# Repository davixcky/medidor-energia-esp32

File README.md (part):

# Medidor de energía eléctrica no invasivo de dos canales con ESP32

**Avance 2 del proyecto de aula (ABPr) — Corte 2**

Sistemas Embebidos 1 · Ingeniería Electrónica · Universidad de la Costa (CUC) · Periodo 2026-2

**Integrantes:** David Orozco · Jose Torres · Leo Rojas

---

## Revisión B — fabricación e interfaz local

La revisión B incorpora gabinete PETG con tapa magnética, LCD Waveshare a color, cuatro
NeoPixels, piezo y encoder para brillo, sonido y umbral de alerta. Las comprobaciones son de
software y CAD; faltan montaje y validación eléctrica. La posición USB-C requiere medir la placa real.

- [Descargas v1.3.0: video con voz y música, CAD y archivos P2S](https://github.com/davixcky/medidor-energia-esp32/releases/tag/v1.3.0).
- [Ficha del dispositivo](freecad/revision-b/medidor-revB.pdf) y [guía de montaje](freecad/revision-b/LEER-ANTES-DE-IMPRIMIR.txt).
- [Firmware y uso del encoder](firmware/README.md#configuración-con-encoder-v130).
- [Fuentes del video](video/revision-b/LEEME.txt).

Los STL y fuentes editables están en Git. El video, la escena Blender y los paquetes de
fabricación se publican como archivos de la release; las cachés y fotogramas se regeneran.
La PCB principal conserva su revisión anterior: encoder, NeoPixels y piezo requieren el
cableado y circuito auxiliar indicados en la guía.

## Contenido

1. [Introducción](#1-introducción)
2. [Objetivos](#2-objetivos)
3. [Planteamiento del problema](#3-planteamiento-del-problema)
4. [Marco teórico](#4-marco-teórico)
5. [Estado del arte](#5-estado-del-arte)
6. [Listado de materiales](#6-listado-de-materiales)
7. [Componente técnico](#7-componente-técnico)
8. [Verificación de la metodología y del cronograma](#8-verificación-de-la-metodología-y-del-cronograma)
9. [Referencias](#9-referencias)
10. [Anexo: archivos fuente y cómo regenerar las ilustraciones](#10-anexo-archivos-fuente-y-cómo-regenerar-las-ilustraciones)

---

## 1. Introducción

Cuando una vivienda o un local comercial no cuenta con medición adicional, la factura informa el
consumo mensual total con hasta treinta días de retraso. Ese dato no permite identificar el consumo
por carga ni por hora, y dificulta evaluar las medidas de ahorro. En la región Caribe, el uso del aire
acondicionado durante el año representa una parte importante del consumo [1].

Este proyecto tiene como objetivo desarrollar un medidor de energía monofásico de 120 V / 60 Hz basado en el microcontrolador
**ESP32**. La medida es **no invasiva**: la corriente se obtiene con pinzas de núcleo partido
**SCT-013-000** que abrazan el conductor de fase sin abrir el circuito, y la tensión con un módulo
**ZMPT101B** que la reduce mediante un transformador aislado. El sistema tiene **dos canales de
corriente** —CH1 para el total del tablero y CH2 para un subcircuito, por ejemplo el del aire
acondicionado— y **un canal de tensión**. El ESP32 digitaliza las tres señales con su convertidor
interno, calcula tensión y corriente eficaces, potencia activa, reactiva y aparente y factor de
potencia, y publica los resultados por Wi-Fi.

Este documento corresponde al segundo avance. Presenta el diseño eléctrico en KiCad, los cálculos de
los componentes, el diseño y los archivos de fabricación de la PCB de una cara, el diseño del gabinete,
el protocolo de pruebas y el estado del cronograma. El montaje del prototipo está pendiente. El
*firmware* y la plataforma se han probado con señales sintéticas y datos simulados; falta validarlos
con el equipo físico en el tercer corte.

## 2. Objetivos

### 2.1. Objetivo general

Desarrollar un medidor de energía eléctrica monofásico y no invasivo, basado en ESP32, con dos canales
de corriente y un canal de tensión aislado, montado en una PCB de una cara dentro de un gabinete con la
zona de red separada, que calcule tensión y corriente eficaces, potencias activa, reactiva y aparente y
factor de potencia por canal, y los publique por Wi-Fi.

### 2.2. Objetivos específicos

1. **Diseñar** la cadena de acondicionamiento (resistencia de carga, polarización, filtro antialias y
   protección) y el esquemático completo en KiCad, sin errores en la verificación eléctrica (ERC), de
   modo que 60 A en CH1 y 30 A en CH2 queden dentro de la zona lineal del ADC1 del ESP32.
2. **Construir** el prototipo en una PCB de una cara fabricada por el grupo, integrado con el microcontrolador dentro del
   gabinete, y aprobar la verificación previa a la energización y la prueba de resistencia
   (*HardExplosion*).
3. **Programar y validar** el *firmware* de adquisición y cálculo (8.000 muestras por segundo por canal,
   ventanas de ciclos completos) y el envío de los registros a la plataforma web, con un error de potencia activa de ±3 % o
   menos frente a una carga resistiva de potencia conocida entre 1 A y 30 A.

## 3. Planteamiento del problema

El Sistema Interconectado Nacional sigue aumentando su demanda año tras año, y la región Caribe consume
una fracción de la energía nacional mayor que su fracción de la población; en los edificios
comerciales de la región el aire acondicionado representa en promedio cerca de la mitad del consumo
total [1]. La factura residencial o comercial presenta el consumo mensual registrado por el contador, sin
desglosarlo por circuito o equipo.

Esa lectura tiene tres limitaciones:

- **Resolución temporal de un mes.** No muestra los ciclos diario y semanal, que son los que dominan en
  un clima sin estaciones.
- **Agregación total.** No distingue qué circuito o qué equipo produjo el consumo, de modo que la factura
  no puede atribuirse a cargas concretas.
- **Latencia.** El usuario conoce su consumo hasta treinta días después, y una acción de ahorro no se
  puede verificar antes del siguiente ciclo de facturación.

Algunos medidores comerciales con Wi-Fi permiten consultar el consumo, pero tienen una arquitectura
cerrada y no dan acceso a la forma de onda ni al método de cálculo. Esto limita su uso para estudiar
la cadena de medición en el curso de sistemas embebidos, desde el sensor y el acondicionamiento hasta
la conversión analógica-digital, el procesamiento y la comunicación.

**Pregunta del proyecto:** ¿cómo medir, con un microcontrolador de bajo costo y sin intervenir la
instalación, el consumo de una edificación por circuito y en tiempo casi real, de forma segura para el
usuario y con un error conocido?

> **Alineación con el primer entregable.** El primer entregable definió un nodo ESP32 con tres pinzas y
> un canal de tensión. Para el alcance de esta asignatura se implementan **dos canales de corriente**
> (total y un subcircuito) y el tercero queda como reserva cableada en el conector J7, que expone las
> entradas GPIO34, GPIO32 y GPIO33 del ADC1 (sección 7.3). El problema, la arquitectura y los criterios
> de seguridad no cambian.

## 4. Marco teórico

### 4.1. Magnitudes eléctricas en régimen periódico

Para una tensión $v(t)$ y una corriente $i(t)$ periódicas de periodo $T$ (16,67 ms a 60 Hz), los valores
eficaces y la potencia activa se definen como [6]:

$$V_{rms} = \sqrt{\frac{1}{T}\int_0^T v^2(t)\,dt}, \qquad I_{rms} = \sqrt{\frac{1}{T}\int_0^T i^2(t)\,dt}, \qquad P = \frac{1}{T}\int_0^T v(t)\,i(t)\,dt$$

La potencia aparente es $S = V_{rms} I_{rms}$, el factor de potencia es $FP = P/S$ y, en régimen
sinusoidal, la potencia reactiva es $Q = \sqrt{S^2 - P^2}$. Con muestras discretas tomadas a la
frecuencia $f_s$, las integrales se reemplazan por sumas sobre un número **entero** de ciclos, lo que
evita el error de truncamiento de la ventana:

$$V_{rms} \approx \sqrt{\frac{1}{N}\sum_{n=0}^{N-1} v_n^2}, \qquad P \approx \frac{1}{N}\sum_{n=0}^{N-1} v_n\, i_n$$

La norma IEEE 1459 [6] extiende estas definiciones a señales no sinusoidales, en las que aparecen
armónicos; es el caso de las fuentes conmutadas y de los equipos con variador de frecuencia.

### 4.2. Transformador de corriente de núcleo partido

Un transformador de corriente (TC) entrega en su secundario una corriente proporcional a la del
primario, en la relación inversa del número de espiras. El SCT-013-000 tiene relación 100 A : 50 mA, es
decir $N = 2000$ espiras, y **no incluye resistencia de carga interna** [2]. El conductor de fase que
atraviesa el núcleo actúa como primario de una sola espira:

$$I_s = \frac{I_p}{N}$$

Para convertir esa corriente en tensión se conecta una resistencia de carga (en inglés, *burden*)
$R_b$ entre los terminales del secundario: $V_b = I_s R_b$.

**Riesgo del secundario abierto.** Si el secundario queda abierto mientras el primario conduce, toda la
fuerza magnetomotriz del primario magnetiza el núcleo, este se satura y en los terminales aparecen
picos de tensión peligrosos para las personas y para el ADC. Por eso la resistencia de carga va soldada
directamente en el conector y nunca en un cable que se pueda desconectar [10].

### 4.3. Medición aislada de la tensión

El ZMPT101B es un transformador de tensión de pequeña señal, con relación 1000:1000 y aislamiento
galvánico entre primario y secundario [3]. El módulo comercial agrega en serie con el primario una
resistencia que limita la corriente, y en el secundario un amplificador LM358 con un potenciómetro de
ganancia. La salida es una sinusoide montada sobre la mitad de la tensión de alimentación, 2,5 V si el
módulo se alimenta con 5 V. Es la **única** pieza del sistema conectada galvánicamente a la red; todo
lo demás opera en muy baja tensión.

### 4.4. Muestreo, aliasing y filtro antialias

El teorema de muestreo [9] exige $f_s > 2 f_{max}$ para reconstruir una señal sin ambigüedad. Si se
quieren observar armónicos hasta el orden 50 (3.000 Hz), se necesita $f_s > 6.000$ muestras/s. El
proyecto usa **8.000 muestras/s por canal**, es decir 133 muestras por ciclo de 60 Hz. Las componentes
por encima de $f_s/2$ se "pliegan" dentro de la banda útil. Para evitarlo, cada canal tiene un filtro RC
pasa-bajas de primer orden:

$$f_c = \frac{1}{2\pi R C}$$

Como la potencia activa depende del producto $v \cdot i$, un desfase $\Delta\varphi$ entre los filtros de
tensión y de corriente produce un error relativo en $P$ cercano a $\tan\varphi \cdot \Delta\varphi$. Por eso
los tres filtros deben tener constantes de tiempo casi iguales.

### 4.5. ADC del ESP32

El ESP32 tiene dos convertidores SAR de 12 bits. El **ADC2 no se puede usar mientras el Wi-Fi está
activo**, porque el controlador de radio lo ocupa [5]; en consecuencia, todas las entradas analógicas de
este proyecto están en el **ADC1** (GPIO32 a GPIO39). Con atenuación de 11 dB el rango útil y lineal
va de unos 0,15 V a 2,45 V [5]. Fuera de ese rango la curva de conversión se vuelve no lineal. Las
señales bipolares de la red se desplazan entonces a un nivel de reposo positivo (polarización) para que
la excursión completa caiga dentro de esa ventana.

### 4.6. Seguridad eléctrica

El Reglamento Técnico de Instalaciones Eléctricas (RETIE) [8] establece la separación entre circuitos de
red y de muy baja tensión (MBT), la protección contra sobrecorriente y el código de colores de los
conductores. El diseño del prototipo contempla cuatro criterios:

1. La red de 120 V nunca entra a la PCB: llega solo al módulo ZMPT101B, ubicado en un
   compartimento separado del gabinete por un tabique.
2. La rama de tensión está protegida con un fusible lento de 500 mA.
3. Las pinzas abrazan únicamente el conductor de fase y no se abre ningún circuito para instalarlas.
4. No se energiza el equipo sin una verificación de aislamiento firmada por dos integrantes
   (sección 7.9).

## 5. Estado del arte

La **Tabla 1** resume soluciones comerciales y abiertas para medir consumo eléctrico, comparadas en las
características que interesan a este proyecto.

**Tabla 1.** Comparación de medidores de energía existentes.

| Solución | Medición | Canales | Procesamiento y comunicación | Acceso a la forma de onda | Observación |
|---|---|---|---|---|---|
| Shelly EM [11] | Pinzas de corriente y tensión directa | 2 | Integrado; Wi-Fi | No | Comercial, muy cercana en alcance a este proyecto |
| Emporia Vue [12] | 2 TC principales y hasta 16 TC por circuito | Hasta 18 | Integrado; Wi-Fi y nube propia | No | Cerrado, orientado al consumidor |
| Sense [13] | 2 TC de 200 A | 2 | Muestreo de alta frecuencia y desagregación de cargas | No para el usuario | Identifica equipos por su firma eléctrica (NILM) [7] |
| IoTaWatt [14] | TC y transformador de tensión externo | 14 | ESP8266 con ADC externo; Wi-Fi | Parcial | *Hardware* y *software* abiertos |
| OpenEnergyMonitor emonTx [10] | TC SCT-013 y adaptador de CA | 3 a 6 | Microcontrolador AVR; radio | Sí | Referencia de diseño del acondicionamiento con resistencia de carga y divisor de polarización |
| PZEM-004T v3.0 [15] | TC propio y conexión directa a red | 1 | Integrado; Modbus-RTU | No | Módulo económico, entrega valores ya calculados una vez por segundo |
| Integrado de metrología ATM90E32AS [16] | Requiere acondicionamiento externo | 3 fases | ADC sigma-delta simultáneos; SPI | No (registros) | Exactitud de contador; procesamiento interno no accesible; requiere importación |
| **Este proyecto** | **2 SCT-013-000 + ZMPT101B** | **2 + 1 tensión** | **ESP32, ADC1 interno; Wi-Fi y HTTP** | **Sí, 8.000 muestras/s por canal** | **Arquitectura abierta; cálculo implementado por el grupo** |

Fuente: elaboración propia a partir de la documentación de cada producto.

Del análisis se concluye que:

- Las soluciones comerciales sin acceso a las muestras ni al método de cálculo limitan el estudio
  de la cadena de adquisición, que forma parte del objetivo académico de la asignatura.
- Los proyectos abiertos (OpenEnergyMonitor, IoTaWatt) validan el enfoque de **pinza SCT-013 +
  resistencia de carga + divisor de polarización + ADC del microcontrolador**, que es el adoptado aquí.
- El acceso a las muestras sin procesar permitiría aplicar técnicas de desagregación de cargas
  (NILM) [7], que los módulos cerrados como el PZEM-004T no permiten.

## 6. Listado de materiales

La **Tabla 2** lista todos los materiales del prototipo. Las referencias de componente coinciden con el
esquemático de la Ilustración 2.

**Tabla 2.** Lista de materiales.

| # | Referencia | Descripción | Cant. | Uso |
|---:|---|---|---:|---|
| 1 | U1 | Tarjeta ESP32-DevKitC V4, 38 pines (ESP32-WROOM-32) | 1 | Microcontrolador, ADC y Wi-Fi |
| 2 | — | Pinza de corriente YHDC SCT-013-000, 100 A : 50 mA, sin resistencia de carga | 2 | Medición de corriente CH1 y CH2 |
| 3 | U2 | Módulo sensor de tensión ZMPT101B (con LM358 y potenciómetro) | 1 | Medición aislada de tensión |
| 4 | — | Pantalla LCD Waveshare de 1,9" (ST7789V2, 170 × 320, SPI), con su cable de 8 hilos | 1 | Lectura local |
| 5 | — | Baquelita de una cara de 10 × 15 cm (FR-2 o FR-4), percloruro férrico, papel de transferencia y alambre UTP para los puentes | 1 | PCB del circuito (sección 7.7) |
| 6 | — | Adaptador 100–240 V CA a 5,1 V CC (5,0–5,25 V), 2 A o más, con aislamiento certificado | 1 | Alimentación |
| 7 | — | *Jack* de panel para alimentación de 5,5 × 2,1 mm | 1 | Entrada de 5 V en el gabinete |
| 8 | J2, J3 | *Jack* estéreo hembra de 3,5 mm para panel | 2 | Conexión de las pinzas |
| 9 | J1 | Bornera de 2 polos, paso 5,08 mm | 1 | Entrada de 5 V en la placa |
| 10 | J5 | Bornera de 3 polos, paso 5,08 mm | 1 | Cable del módulo ZMPT101B |
| 11 | J4 | Regleta de 2 bornes de tornillo | 1 | Empalme de fase y neutro en la zona de red |
| 12 | F1 | Portafusible de 5 × 20 mm y fusible lento T 500 mA, 250 V | 1 + 1 de repuesto | Protección de la rama de tensión |
| 13 | F2 | Fusible PTC de rearme automático MF-R110 (1,1 A de mantenimiento) | 1 | Protección contra cortocircuito en 5 V |
| 14 | D1 | Diodo Schottky 1N5819 | 1 | Protección contra polaridad invertida |
| 15 | D2–D7 | Diodo Schottky BAT85 (DO-35) | 6 | Recorte de sobretensión en las entradas del ADC |
| 16 | R1 | Resistencia 22 Ω, 1 %, película metálica, 1/4 W | 1 | Resistencia de carga CH1 |
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
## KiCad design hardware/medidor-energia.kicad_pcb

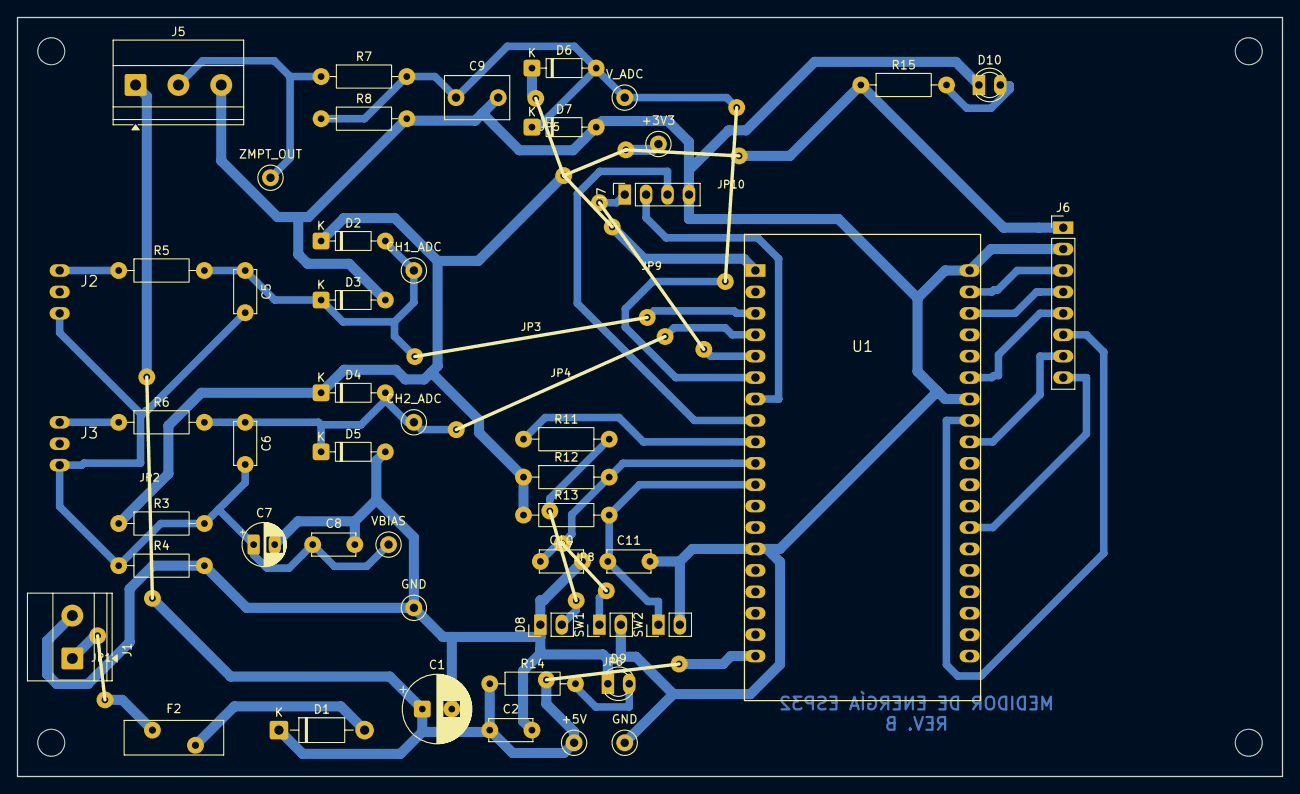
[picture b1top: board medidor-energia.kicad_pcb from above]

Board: 2 copper layers, 150.0 x 90.0 mm, 63 parts (0 on the bottom side), 27 nets.

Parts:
C1: 470u 10V; CP_Radial_D8.0mm_P3.50mm
C2, C8, C10, C11: 100n; C_Disc_D5.0mm_W2.5mm_P5.00mm
C5, C6: 47n C0G; C_Disc_D5.0mm_W2.5mm_P5.00mm
C7: 10u 16V; CP_Radial_D5.0mm_P2.50mm
C9: 27n C0G; C_Disc_D7.5mm_W5.0mm_P5.00mm
D1: 1N5819; D_DO-41_SOD81_P10.16mm_Horizontal
D2, D3, D4, D5, D6, D7: BAT85; D_DO-35_SOD27_P7.62mm_Horizontal
D8: LED verde 5 mm (panel); PinHeader_1x02_P2.54mm_Vertical
D9: LED rojo 3 mm; LED_D3.0mm
D10: LED verde 3 mm; LED_D3.0mm
F2: PTC 1,1 A (MF-R110); Fuse_BelFuse_0ZRE0040FF_L11.5mm_W3.8mm
H1, H2, H3, H4: MountingHole_3.2mm_M3
J1: Bornera 5 V; TerminalBlock_Phoenix_MKDS-1,5-2-5.08_1x02_P5.08mm_Horizont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
J2: Jack 3,5 mm de panel (pinza SCT-013-000 CH1); Cable_Jack_Panel
J3: Jack 3,5 mm de panel (pinza SCT-013-000 CH2); Cable_Jack_Panel
J5: Bornera ZMPT; TerminalBlock_Phoenix_MKDS-1,5-3-5.08_1x03_P5.08mm_Horizont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
J6: LCD (VCC GND DIN CS DC BL CLK RST); PinHeader_1x08_P2.54mm_Vertical
J7: Reserva ADC1; PinSocket_1x04_P2.54mm_Vertical
JP1, JP2, JP3, JP4, JP5, JP6, JP7, JP8, JP9, JP10: puente; Puente_alambre
R3: 15k 1%; R_Axial_DIN0207_L6.3mm_D2.5mm_P10.16mm_Horizontal
R4: 10k 1%; R_Axial_DIN0207_L6.3mm_D2.5mm_P10.16mm_Horizontal
R5, R6: 3,3k 1%; R_Axial_DIN0207_L6.3mm_D2.5mm_P10.16mm_Horizontal
R7: 11k 1%; R_Axial_DIN0207_L6.3mm_D2.5mm_P10.16mm_Horizontal
R8: 13k 1%; R_Axial_DIN0207_L6.3mm_D2.5mm_P10.16mm_Horizontal
R11: 330; R_Axial_DIN0207_L6.3mm_D2.5mm_P10.16mm_Horizontal
R12, R13: 10k; R_Axial_DIN0207_L6.3mm_D2.5mm_P10.16mm_Horizontal
R14: 1k; R_Axial_DIN0207_L6.3mm_D2.5mm_P10.16mm_Horizontal
R15: 470; R_Axial_DIN0207_L6.3mm_D2.5mm_P10.16mm_Horizontal
SW1, SW2: Pulsador de panel 12 mm NA; PinHeader_1x02_P2.54mm_Vertical
TP1: +5V; TestPoint_Loop_D2.50mm_Drill1.0mm
TP2: +3V3; TestPoint_Loop_D2.50mm_Drill1.0mm
TP3: VBIAS; TestPoint_Loop_D2.50mm_Drill1.0mm
TP4: CH1_ADC; TestPoint_Loop_D2.50mm_Drill1.0mm
TP5: CH2_ADC; TestPoint_Loop_D2.50mm_Drill1.0mm
TP6: ZMPT_OUT; TestPoint_Loop_D2.50mm_Drill1.0mm
TP7: V_ADC; TestPoint_Loop_D2.50mm_Drill1.0mm
TP8, TP9: GND; TestPoint_Loop_D2.50mm_Drill1.0mm
U1: ESP32-DevKitC V4 (38 pines); ESP32-DevKitC-38_Zocalo

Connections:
+3V3: D2.1, D4.1, D6.1, J6.1, JP5.1, R3.1, R12.1, R13.1, R15.1, TP2.1, U1.1
+5V: C1.1, C2.1, D1.1, J5.1, JP2.1, JP6.1, R14.1, TP1.1, U1.19
/CH1_ADC: C5.1, D2.2, D3.1, JP3.1, R5.2, TP4.1, U1.3
/CH2_ADC: C6.1, D4.2, D5.1, JP4.1, R6.2, TP5.1, U1.4
/LCD_BL: J6.6, U1.27
/LCD_CLK: J6.7, U1.28
/LCD_CS: J6.4, U1.22
/LCD_DC: J6.5, U1.25
/LCD_DIN: J6.3, U1.21
/LCD_RST: J6.8, U1.32
/LED_EST: R11.1, U1.9
/RES_IO32: J7.2, U1.7
/RES_IO33: J7.3, U1.8
/RES_IO34: J7.1, JP9.1, U1.5
/SW1: C10.1, JP8.1, R12.2, SW1.1, U1.10
/SW2: C11.1, R13.2, SW2.1, U1.11
/VBIAS: C5.2, C6.2, C7.1, C8.1, J2.S, J3.S, R3.2, R4.1, TP3.1
/V_ADC: C9.1, D6.2, D7.1, JP10.1, R7.2, R8.1, TP7.1, U1.6
/ZMPT_OUT: J5.2, R7.1, TP6.1
GND: C1.2, C2.2, C7.2, C8.2, C9.2, C10.2, C11.2, D3.2, D5.2, D7.2, D8.1, D9.1, D10.1, J1.2, J5.3, J6.2, J7.4, R4.2, R8.2, SW1.2, SW2.2, TP8.1, TP9.1, U1.14, U1.20, U1.26
unnamed: D1.2, F2.2
unnamed: D8.2, JP7.1, R11.2
unnamed: D9.2, R14.2
unnamed: D10.2, R15.2
unnamed: F2.1, J1.1, JP1.1
unnamed: J2.T, R5.1
unnamed: J3.T, R6.1

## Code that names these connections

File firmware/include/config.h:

// Configuración del hardware y constantes de calibración.
// Los pines coinciden con la Tabla 3 del documento y con el esquemático.
#pragma once
#include <driver/adc.h>

// ---- Entradas analógicas (solo ADC1: el ADC2 no funciona con Wi-Fi)
constexpr adc1_channel_t ADC_CH1 = ADC1_CHANNEL_0;  // GPIO36, pinza CH1 (total)
constexpr adc1_channel_t ADC_CH2 = ADC1_CHANNEL_3;  // GPIO39, pinza CH2 (subcircuito)
constexpr adc1_channel_t ADC_V   = ADC1_CHANNEL_7;  // GPIO35, ZMPT101B

// ---- Interfaz local
constexpr int ENCODER_EDGES_PER_DETENT = 4; // elegir 2 si la ficha indica medio ciclo por paso
static_assert(ENCODER_EDGES_PER_DETENT == 2 || ENCODER_EDGES_PER_DETENT == 4, "Encoder: 2 o 4 flancos por paso");
constexpr int PIN_ENC_A = 32;
constexpr int PIN_ENC_B = 33;
constexpr int PIN_ENC_SW = 16; // ESP32-WROOM; no WROVER con PSRAM en GPIO16
constexpr int PIN_NEOPIXEL = 13; // módulo auxiliar, vía 74AHCT125 a 5 V
constexpr int PIN_BUZZER = 14;   // piezo pasivo vía transistor; PWM canal 2
constexpr int PIN_LED = 25;
constexpr int PIN_SW1 = 26;   // menú / canal (activo en bajo, pull-up externo de 10 kΩ)
constexpr int PIN_SW2 = 27;   // confirmar / tara
// LCD Waveshare de 1,9" (ST7789V2, 170 × 320) por SPI. Todos los pines están en el mismo lado
// de la tarjeta (J3 del DevKitC); se evitan GPIO5 y GPIO15, que son pines de arranque.
constexpr int PIN_LCD_CLK = 18;   // SCK del VSPI
constexpr int PIN_LCD_DIN = 23;   // MOSI del VSPI
constexpr int PIN_LCD_CS = 22;
constexpr int PIN_LCD_DC = 21;
constexpr int PIN_LCD_RST = 4;
constexpr int PIN_LCD_BL = 19;    // luz de fondo, con PWM
constexpr uint32_t LCD_SPI_HZ = 40000000;

// ---- Muestreo
constexpr uint32_t FS_HZ = 8000;        // muestras por segundo y por canal
constexpr int CICLOS_VENTANA = 60;      // ventana de 60 ciclos enteros (1 s a 60 Hz)
constexpr uint32_t DESCARTE_MS = 500;   // espera a que se estabilice VBIAS al encender

// ---- Calibración nominal. Son los valores por omisión: los que se miden en el banco se guardan en
// la memoria no volátil desde la consola serie (comando «cal», ver README del firmware) y no hace
// falta recompilar.
// Corriente: A de primario por voltio en el pin = relación 2000 / resistencia de carga.
constexpr float K_I1 = 2000.0f / 22.0f;   // CH1, burden 22 Ω
constexpr float K_I2 = 2000.0f / 47.0f;   // CH2, burden 47 Ω
// Tensión: V de red por voltio en el pin. 120 V eficaces → 0,352 V pico en el pin
// (potenciómetro del módulo en 0,65 V pico y divisor 13/24): 169,7 / 0,352 = 482.
constexpr float K_V = 482.0f;
// Corrección de fase en grados a 60 Hz: de cada pinza (positivo = la corriente adelanta) y del
// canal de tensión, transformador y LM358 del ZMPT101B (positivo = la tensión adelanta). Se mide
// en el banco con una carga inductiva o contra el PZEM-004T; con carga resistiva no se ve.
constexpr float FASE_CT1_GRADOS = 0.0f;
constexpr float FASE_CT2_GRADOS = 0.0f;
constexpr float FASE_V_GRADOS = 0.0f;
// Constante de tiempo de los filtros antialias (para compensar armónicos en el THD).
constexpr float TAU_FILTRO_S = 156e-6f;

// ---- Alerta local (el servidor calcula el umbral P95; esto es el respaldo sin red)
constexpr float UMBRAL_ALERTA_W = 2000.0f;
constexpr uint32_t ALERTA_SOSTENIDA_S = 300;

// ---- Red
constexpr uint32_t ENVIO_CADA_MS = 5000;    // lote de registros cada 5 s
constexpr size_t BUFER_REGISTROS = 1200;    // 20 min sin red en RAM (48 kB)

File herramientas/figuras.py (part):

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    ct2  [label="Pinza SCT-013-000 CH2\n(subcircuito, 0–30 A)", fillcolor="#fff8e1"];
    b1   [label="Burden 22 Ω\n+ RC 3,3 kΩ / 47 nF\n+ recorte BAT85", fillcolor="#fff8e1"];
    b2   [label="Burden 47 Ω\n+ RC 3,3 kΩ / 47 nF\n+ recorte BAT85", fillcolor="#fff8e1"];
    bias [label="VBIAS 1,32 V\ndivisor 15k/10k", fillcolor="#f3e5f5"];
    div  [label="Divisor 11k/13k\n+ C 27 nF\n+ recorte BAT85", fillcolor="#e8f5e9"];
    esp  [label="U1  ESP32-DevKitC V4\nADC1 12 bit · Wi-Fi\nGPIO36 / 39 / 35", fillcolor="#e3f2fd", penwidth=2];
    oled [label="LCD 1,9\" ST7789V2\n170 × 320, SPI", fillcolor="#e3f2fd"];
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  ct1 -> b1 [label="0–30 mA", color="#b8860b"];
  ct2 -> b2 [label="0–15 mA", color="#b8860b"];
  bias -> b1 [color="#8e24aa"]; bias -> b2 [color="#8e24aa"];
  b1 -> esp [label="CH1_ADC\nGPIO36", color="#b8860b"];
  b2 -> esp [label="CH2_ADC\nGPIO39", color="#b8860b"];
  div -> esp [label="V_ADC\nGPIO35", color="#2e7d32"];
  esp -> oled [color="#1565c0", label="SPI\nGPIO18/23/22/21/4/19"];
  esp -> hmi [dir=both, label="GPIO25/26/27"];
  esp -> res [style=dashed];
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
